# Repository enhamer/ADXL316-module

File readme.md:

<!---
#**============================================================================
#**
#**                    Accelerometer ADXL316 MODULE
#**                  THIS REPOSITORY IS PART OF THE ENHAMER
#**
#** TITLE:           ADXL-316 PCB (Circuit, Hardware)
#**
#** AUTHOR:          Marcin J. Kraśny
#**
#**					 Advanced Biological Imaging Laboratory
#**                  School of Physics
#**                  College of Science and Engineering
#**                  National University of Ireland, Galway
#**
#** SOURCE URL       https://github.com/enhamer/enhamer
#** COPYRIGHT        © 2015-2020 M.J.Kraśny
#** LICENSE          CERN-OHL-P v2
#** CREDITS          NEMESIS - Novel Energy Materials, Engineering Science 
#**                  and Integrated Systems
#**                  Department of Mechanical Engineering
#**					 University of Bath, UK
#**
#**============================================================================
#**============================================================================
-->

# ADXL316 module
Part of:
**Energy Harvesting Measurement Rig (ENHAMER)**

*A System for Characterisation of Piezoelectric Materials and Associated Electronics for Vibration Powered Energy Harvesting Devices*

>For detailed **Information, Manuals and Description** please go to [**ENHAMER**](https://github.com/enhamer/enhamer/).

Assembled module mounted on acrylic holder:

## Design software used
[EAGLE CAD](https://www.autodesk.com/products/eagle/overview)

# License
Copyright © 2015-2020 Marcin J. Kraśny

This work is licensed under the [CERN-OHL-P v2](LICENSE/cern_ohl_p_v2.txt); 
[CERN Open Hardware Licence version 2](https://cern.ch/cern-ohl).

You may redistribute and modify this documentation and make products
using it under the terms of the CERN-OHL-P v2 (<https:/cern.ch/cern-ohl>).
This documentation is distributed WITHOUT ANY EXPRESS OR IMPLIED WARRANTY INCLUDING OF MERCHANTABILITY, SATISFACTORY QUALITY AND FITNESS FOR A PARTICULAR PURPOSE. 
Please see the CERN-OHL-P v2 for applicable conditions.

# SOURCE
[https://github.com/enhamer](https://github.com/enhamer/enhamer/)

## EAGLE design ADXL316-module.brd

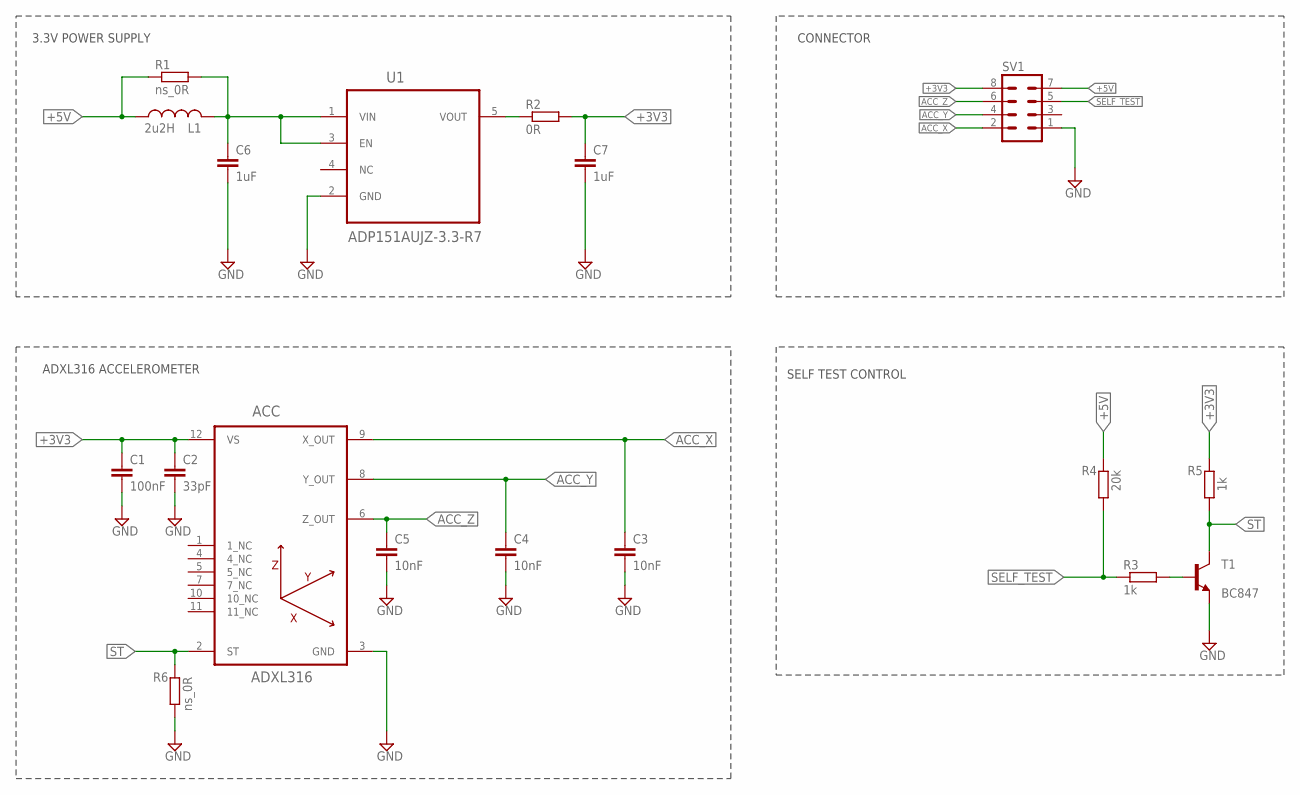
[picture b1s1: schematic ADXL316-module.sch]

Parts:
ACC: ADXL316; QFN24-4X4_MJK
C1: 100nF; 0805
C2: 33pF; 0805
C3, C4, C5: 10nF; 0805
C6, C7: 1uF; 0805
L1: 2u2H; 0805
R1, R6: ns_0R; 0805
R2: 0R; 0805
R3, R5: 1k; 0805
R4: 20k; 0805
SV1: MA04-2
T1: BC847; SOT23
U1: ADP151AUJZ-3.3-R7; SOT95P280X100-5N

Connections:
+3V3: ACC.12 (VS), C1.1, C2.1, C7.1, R2.2, R5.2, SV1.8
+5V: L1.1, R1.1, R4.2, SV1.7
ACC_X: ACC.9 (X_OUT), C3.1, SV1.2
ACC_Y: ACC.8 (Y_OUT), C4.1, SV1.4
ACC_Z: ACC.6 (Z_OUT), C5.1, SV1.6
GND: ACC.3 (GND), C1.2, C2.2, C3.2, C4.2, C5.2, C6.2, C7.2, R6.1, SV1.1, T1.2 (E), U1.2 (GND)
unnamed: C6.1, L1.2, R1.2, U1.1 (VIN), U1.3 (EN)
unnamed: R2.1, U1.5 (VOUT)
unnamed: R3.2, T1.1 (B)
SELF_TEST: R3.1, R4.1, SV1.5
ST: ACC.2 (ST), R5.1, R6.2, T1.3 (C)

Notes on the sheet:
CONNECTOR
3.3V POWER SUPPLY
SELF TEST CONTROL
ADXL316 ACCELEROMETER

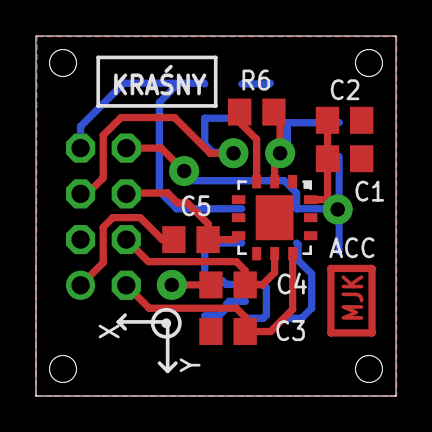
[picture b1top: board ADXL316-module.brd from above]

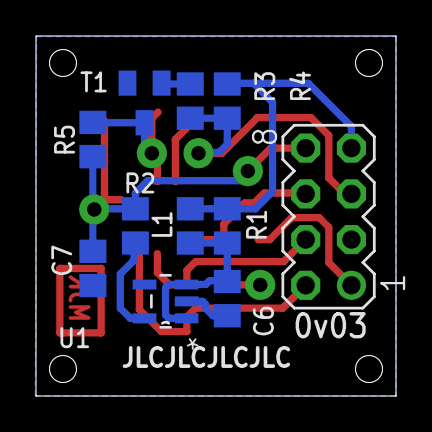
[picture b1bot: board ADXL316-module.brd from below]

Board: 2 copper layers, 20.0 x 20.0 mm, 18 parts (11 on the bottom side), 11 nets.

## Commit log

2020-05-08 ADXL316 module EAGLE PCB design
2020-06-03 License and repo readme update
